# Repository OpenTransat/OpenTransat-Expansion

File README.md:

# OpenTransat-Expansion

The [Navigator](https://github.com/OpenTransat/OpenTransat-Navigator) is mounted on top of Expansion Board that will provide additional functions more specific to the boat. This modular design allows to make quick modifications on the Expansion Board while keeping the more complex Navigation Board unchanged.

## Features

* Watchdog timer that monitors the “heartbeat” of the main CPU. If the Navigator doesn't respond for a minute or it reports any kind of failure, the watchdog will cut power for a few seconds.

* MOSFETs to turn on particular hardware only when needed.

## Boat Hardware Scheme

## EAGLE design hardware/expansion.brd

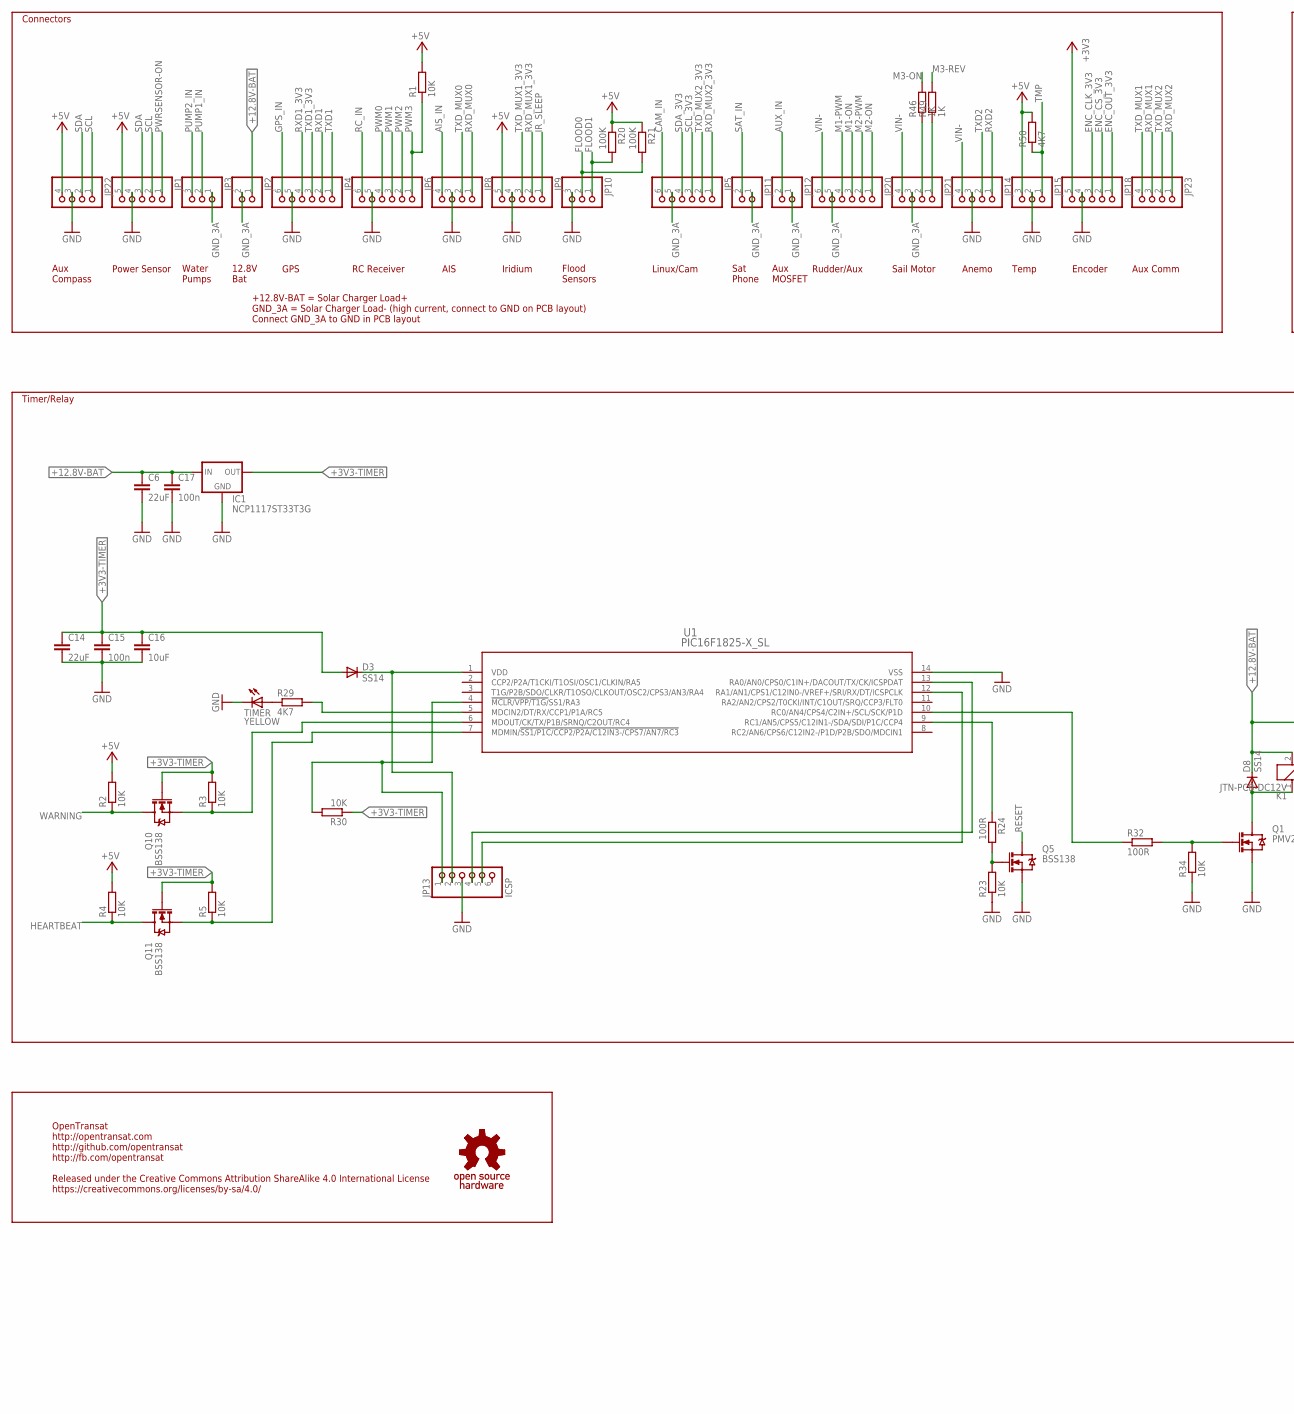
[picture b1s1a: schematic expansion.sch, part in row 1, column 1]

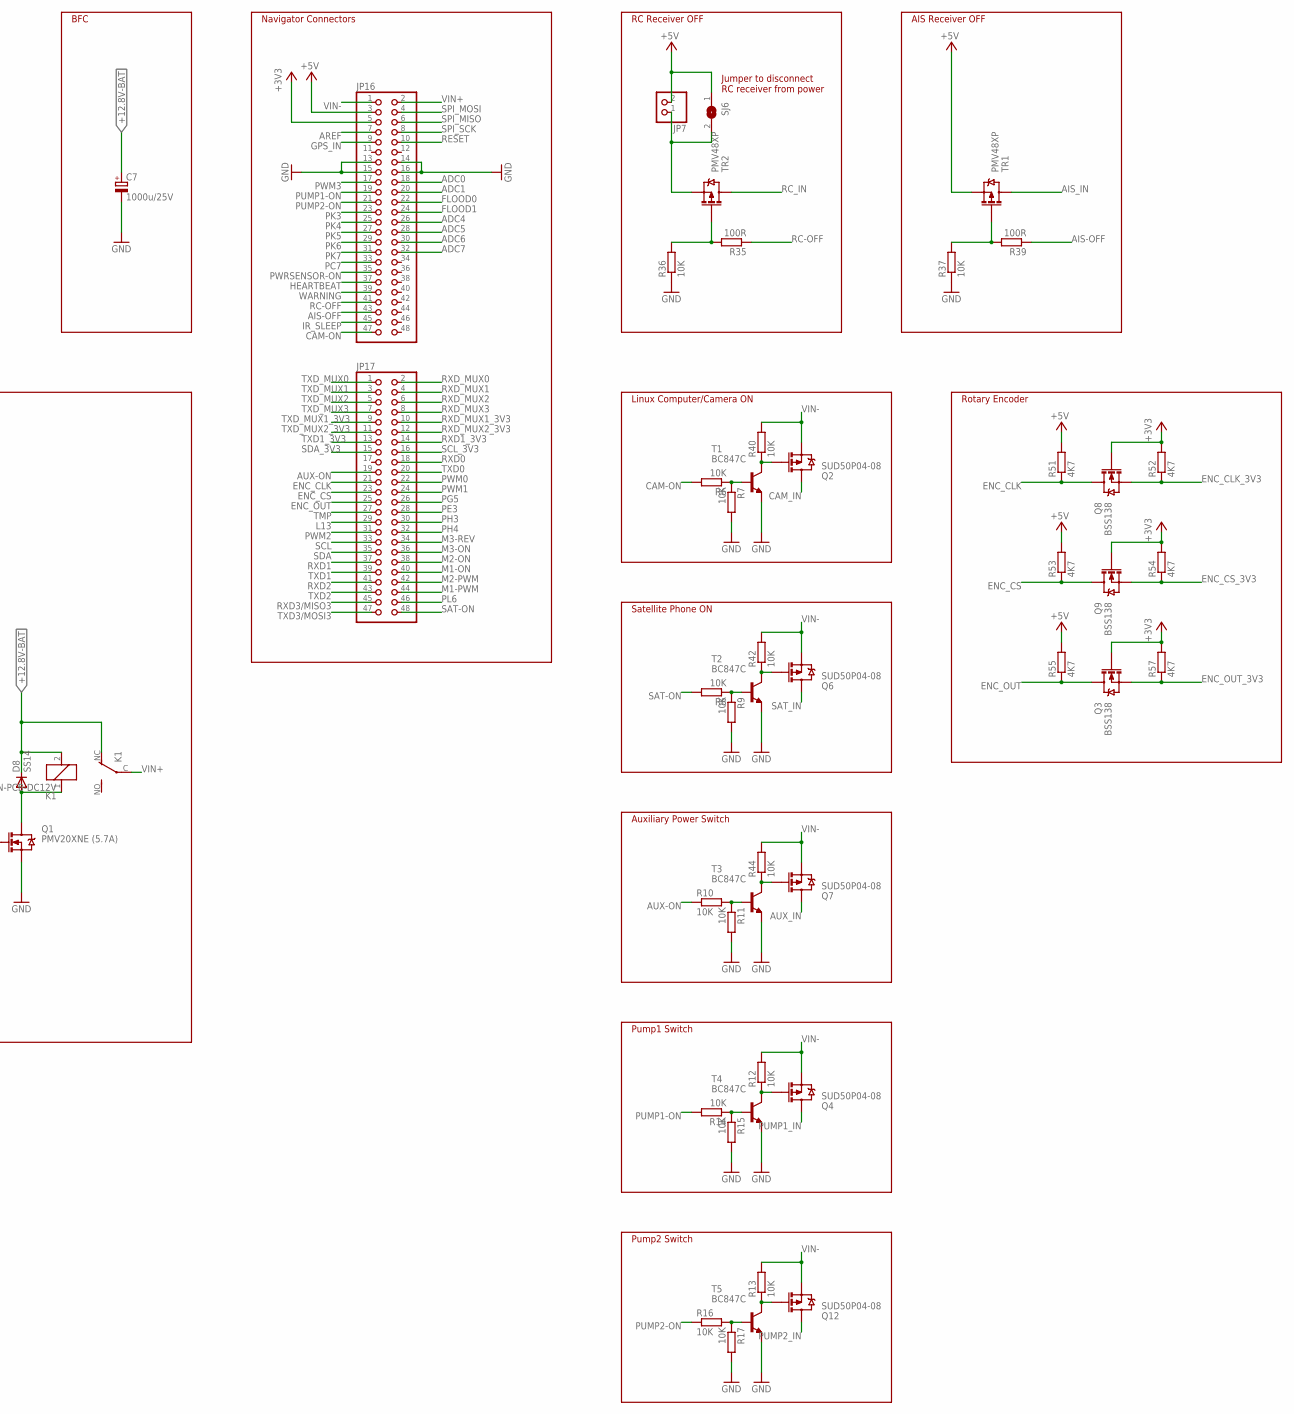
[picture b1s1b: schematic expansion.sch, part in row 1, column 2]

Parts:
C6, C14: 22uF; C1210
C7: 1000u/25V; E5-10,5
C15, C17: 100n; C0603
C16: 10uF; C1206
D3, D8: SS14; DO214AC
IC1: NCP1117ST33T3G; SOT223
JP1, JP9, JP18: PINHD-1X5; 1X05
JP2, JP7, JP11, JP12: PINHD-1X2; 1X02
JP3, JP10, JP15: PINHD-1X3; 1X03
JP4, JP5, JP6, JP20: PINHD-1X6; 1X06
JP8, JP14, JP21, JP22, JP23: PINHD-1X4; 1X04
JP13: ICSP; 1X06
JP16, JP17: PINHD-2X24; 2X24
K1: JTN-PCB-DC12V; JT-PCB
Q1: PMV20XNE (5.7A); SOT23-3
Q2, Q4, Q6, Q7, Q12: SUD50P04-08; D-PAK_TO252AA
Q3, Q5, Q8, Q9, Q10, Q11: BSS138; SOT23-3
R1, R2, R3, R4, R5, R6, R7, R8, R9, R10, R11, R12, R13, R14, R15, R16, R17, R23, R30, R34, R36, R37, R40, R42, R44: 10K; R0603
R20, R21: 100K; R0603
R24, R32, R35, R39: 100R; R0603
R29, R50, R51, R52, R53, R54, R55, R57: 4K7; R0603
R46, R49: 1K; R0603
SJ6: SJ
T1, T2, T3, T4, T5: BC847C; SOT23
TIMER: YELLOW; CHIPLED_0805
TR1, TR2: PMV48XP; SOT23-3
U1: PIC16F1825-X_SL; SOIC14-N_MC
U$2: OSHW; OSHWM

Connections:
+3V3: JP16.5, JP18.5, Q3.1 (G), Q8.1 (G), Q9.1 (G), R52.2, R54.2, R57.2
+3V3-TIMER: C14.1, C15.1, C16.1, D3.A, IC1.2 (OUT), IC1.4 (OUT), Q10.1 (G), Q11.1 (G), R3.2, R5.2, R30.1
+5V: JP1.5, JP7.2, JP9.5, JP15.3, JP16.3, JP22.4, R1.2, R2.2, R4.2, R20.1, R21.1, R50.2, R51.2, R53.2, R55.2, SJ6.1, TR1.2 (S)
+12.8V-BAT: C6.1, C7.+, C17.1, D8.C, IC1.3 (IN), JP2.1, K1.2, K1.NC (O)
ADC0: JP16.18
ADC1: JP16.20
ADC4: JP16.26
ADC5: JP16.28
ADC6: JP16.30
ADC7: JP16.32
AIS-OFF: JP16.43, R39.1
AIS_IN: JP8.4, TR1.3 (D)
AREF: JP16.7
AUX-ON: JP17.19, R10.1
AUX_IN: JP12.2, Q7.2 (D)
CAM-ON: JP16.47, R6.2
CAM_IN: JP5.6, Q2.2 (D)
ENC_CLK: JP17.21, Q8.3 (D), R51.1
ENC_CLK_3V3: JP18.3, Q8.2 (S), R52.1
ENC_CS: JP17.23, Q9.3 (D), R53.1
ENC_CS_3V3: JP18.2, Q9.2 (S), R54.1
ENC_OUT: JP17.25, Q3.3 (D), R55.1
ENC_OUT_3V3: JP18.1, Q3.2 (S), R57.1
FLOOD0: JP10.2, JP16.22, R21.2
FLOOD1: JP10.1, JP16.24, R20.2
GND: C6.2, C7.-, C14.2, C15.2, C16.2, C17.2, IC1.1 (GND), JP1.4, JP4.5, JP6.5, JP8.3, JP9.4, JP10.3, JP13.3, JP14.3, JP15.2, JP16.13, JP16.14, JP16.15, JP16.16, JP18.4, JP22.3, Q1.2 (S), Q5.2 (S), R7.2, R9.2, R11.2, R15.2, R17.2, R23.1, R34.1, R36.1, R37.1, T1.2 (E), T2.2 (E), T3.2 (E), T4.2 (E), T5.2 (E), TIMER.C, U1.14 (VSS)
GND_3A: JP2.2, JP3.1, JP5.5, JP11.1, JP12.1, JP20.5, JP21.3
GPS_IN: JP4.6, JP16.9
HEARTBEAT: JP16.37, Q11.3 (D), R4.1
IR_SLEEP: JP9.1, JP16.45
L13: JP17.29
M1-ON: JP17.40, JP20.3
M1-PWM: JP17.44, JP20.4
M2-ON: JP17.38, JP20.1
M2-PWM: JP17.42, JP20.2
M3-ON: JP17.36, R46.2
M3-REV: JP17.34, R49.2
unnamed: R6.1, R7.1, T1.1 (B)
unnamed: Q10.2 (S), R3.1, U1.6 (MDOUT/CK/TX/P1B/SRNQ/C2OUT/RC4)
unnamed: R8.1, R9.1, T2.1 (B)
unnamed: Q11.2 (S), R5.1, U1.7 (MDMIN/!SS1/P1C/CCP2/P2A/C12IN3-/CPS7/AN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)
unnamed: R10.2, R11.1, T3.1 (B)
unnamed: Q4.1 (G), R12.1, T4.3 (C)
unnamed: Q12.1 (G), R13.1, T5.3 (C)
unnamed: R14.1, R15.1, T4.1 (B)
unnamed: R16.2, R17.1, T5.1 (B)
unnamed: JP21.2, R46.1
unnamed: JP21.1, R49.1
unnamed: JP13.4, U1.13 (RA0/AN0/CPS0/C1IN+/DACOUT/TX/CK/ICSPDAT)
unnamed: Q7.1 (G), R44.1, T3.3 (C)
unnamed: Q6.1 (G), R42.1, T2.3 (C)
unnamed: Q2.1 (G), R40.1, T1.3 (C)
unnamed: JP13.1, R30.2, U1.4 (!MCLR/VPP/T1G/!SS1/RA3)
unnamed: JP13.5, U1.12 (RA1/AN1/CPS1/C12IN0-/VREF+/SRI/RX/DT/IC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)
unnamed: R32.1, U1.10 (RC0/AN4/CPS4/C2IN+/SCL/SCK/P1D)
unnamed: D3.C, JP13.2, U1.1 (VDD)
unnamed: R24.1, U1.9 (RC1/AN5/CPS5/C12IN1-/SDA/SDI/P1C/CCP4)
unnamed: Q5.1 (G), R23.2, R24.2
unnamed: R29.2, U1.5 (MDCIN2/DT/RX/CCP1/P1A/RC5)
unnamed: R29.1, TIMER.A
unnamed: Q1.1 (G), R32.2, R34.2
unnamed: JP7.1, SJ6.2, TR2.2 (S)
unnamed: D8.A, K1.1, Q1.3 (D)
unnamed: R35.2, R36.2, TR2.1 (G)
unnamed: R37.2, R39.2, TR1.1 (G)
PC7: JP16.33
PE3: JP17.28
PG5: JP17.26
PH3: JP17.30
PH4: JP17.32
PK3: JP16.23
PK4: JP16.25
PK5: JP16.27
PK6: JP16.29
PK7: JP16.31
PL6: JP17.46
PUMP1-ON: JP16.19, R14.2
PUMP1_IN: JP3.2, Q4.2 (D)
PUMP2-ON: JP16.21, R16.1
PUMP2_IN: JP3.3, Q12.2 (D)
PWM0: JP6.4, JP17.22
PWM1: JP6.3, JP17.24
PWM2: JP6.2, JP17.31
PWM3: JP6.1, JP16.17, R1.1
PWRSENSOR-ON: JP1.1, JP16.35
RC-OFF: JP16.41, R35.1
RC_IN: JP6.6, TR2.3 (D)
RESET: JP16.10, Q5.3 (D)
RXD0: JP17.18
RXD1: JP4.2, JP17.37
RXD1_3V3: JP4.4, JP17.14
RXD2: JP14.1, JP17.41
RXD3/MISO3: JP17.45
RXD_MUX0: JP8.1, JP17.2
RXD_MUX1: JP17.4, JP23.3
RXD_MUX1_3V3: JP9.2, JP17.10
RXD_MUX2: JP17.6, JP23.1
RXD_MUX2_3V3: JP5.1, JP17.12
RXD_MUX3: JP17.8
SAT-ON: JP17.48, R8.2
SAT_IN: JP11.2, Q6.2 (D)
SCL: JP1.2, JP17.33, JP22.1
SCL_3V3: JP5.3, JP17.16
SDA: JP1.3, JP17.35, JP22.2
SDA_3V3: JP5.4, JP17.15
SPI_MISO: JP16.6
SPI_MOSI: JP16.4
SPI_SCK: JP16.8
TMP: JP15.1, JP17.27, R50.1
TXD0: JP17.20
TXD1: JP4.1, JP17.39
TXD1_3V3: JP4.3, JP17.13
TXD2: JP14.2, JP17.43
TXD3/MOSI3: JP17.47
TXD_MUX0: JP8.2, JP17.1
TXD_MUX1: JP17.3, JP23.4
TXD_MUX1_3V3: JP9.3, JP17.9
TXD_MUX2: JP17.5, JP23.2
TXD_MUX2_3V3: JP5.2, JP17.11
TXD_MUX3: JP17.7
VIN+: JP16.2, K1.C
VIN-: JP14.4, JP16.1, JP20.6, JP21.4, Q2.3 (S), Q4.3 (S), Q6.3 (S), Q7.3 (S), Q12.3 (S), R12.2, R13.2, R40.2, R42.2, R44.2
WARNING: JP16.39, Q10.3 (D), R2.1

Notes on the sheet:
Navigator Connectors
Connectors
Timer/Relay
RC Receiver OFF
AIS Receiver OFF
Linux Computer/Camera ON
Satellite Phone ON
Auxiliary Power Switch
Rotary Encoder
12.8V Bat
GPS
RC Receiver
AIS
Iridium
Flood Sensors
Linux/Cam
Sat Phone
Aux MOSFET
Rudder/Aux
Sail Motor
Anemo
Temp
Encoder
Aux Comm
+12.8V-BAT = Solar Charger Load+ GND_3A = Solar Charger Load- (high current, connect to GND on PCB layout) Connect GND_3A to GND in PCB layout
Water Pumps
BFC
OpenTransat http://opentransat.com http://github.com/opentransat http://fb.com/opentransat Released under the Creative Commons Attribution ShareAlike 4.0 International License https://creativecommons.org/licenses/by-sa/4.0/
Jumper to disconnect RC receiver from power
Pump1 Switch
Pump2 Switch
Aux Compass
Power Sensor

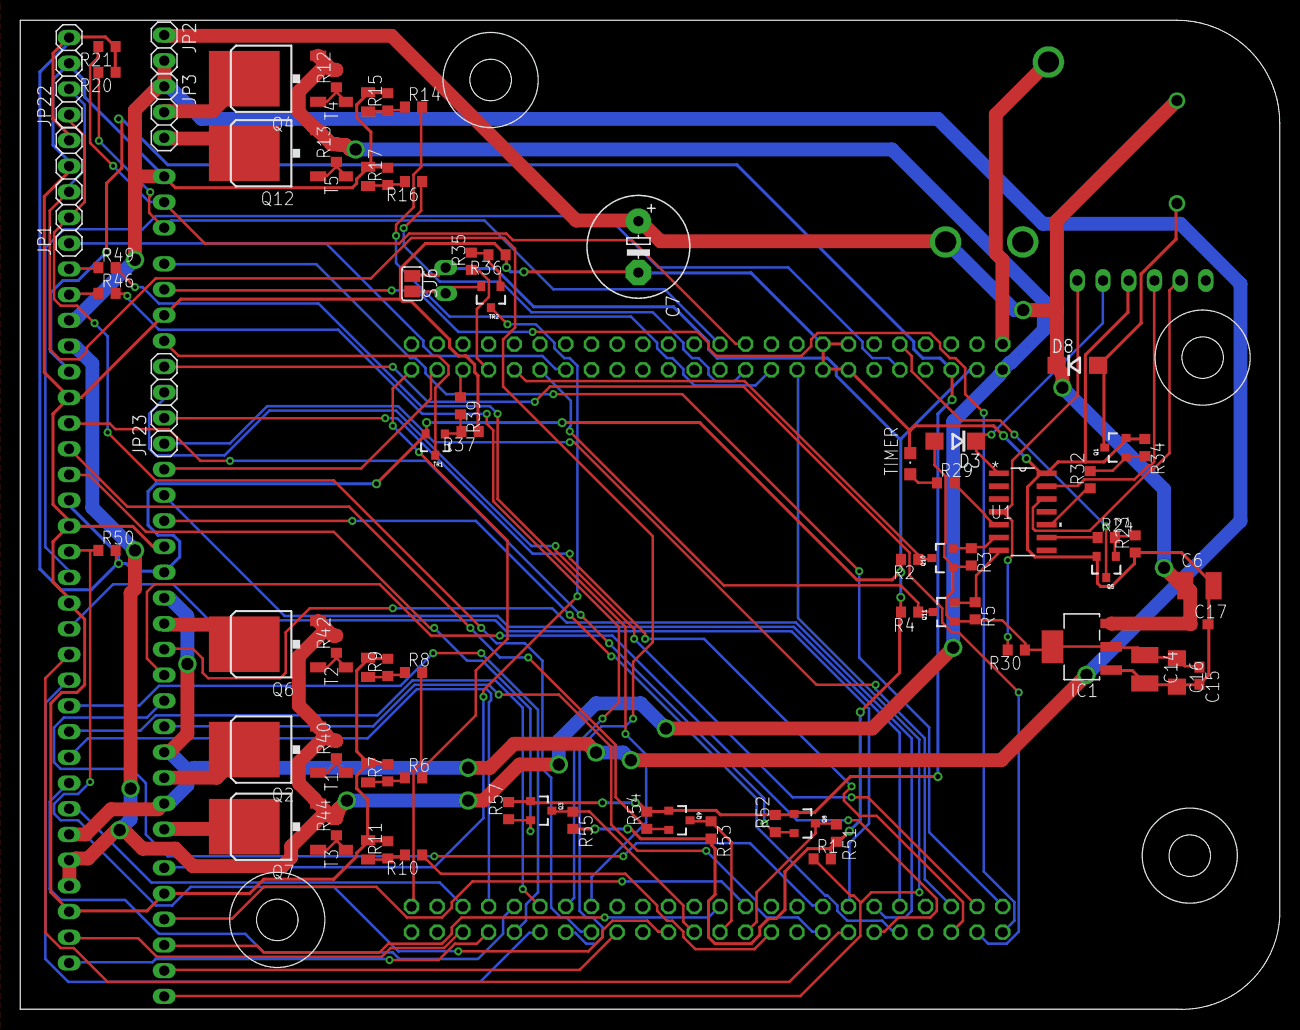
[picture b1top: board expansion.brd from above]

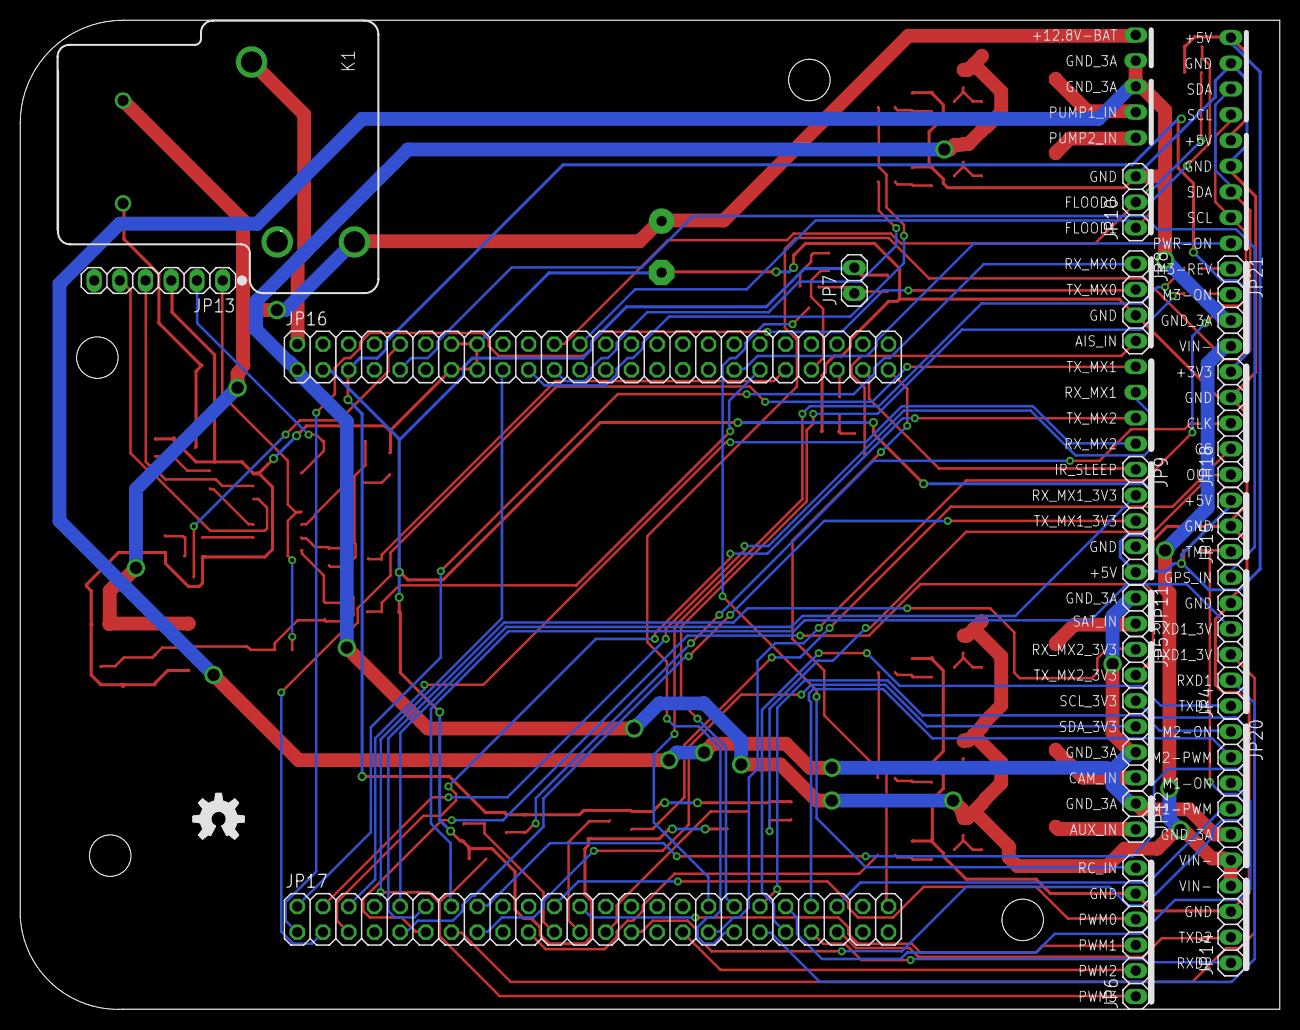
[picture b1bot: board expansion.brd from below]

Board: 2 copper layers, 124.5 x 97.7 mm, 96 parts (18 on the bottom side), 95 nets.

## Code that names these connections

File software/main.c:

/*
Hardware watchdog timer based on PIC16F1825

OpenTransat
http://opentransat.com
http://github.com/opentransat
http://fb.com/opentransat

Released under the Creative Commons Attribution ShareAlike 4.0 International License
https://creativecommons.org/licenses/by-sa/4.0/
*/

#define _XTAL_FREQ 31000UL
#include "config.h"
#include <xc.h>

#define RELAY PORTCbits.RC0
#define NAVRESET PORTCbits.RC1
#define HEARTBEAT PORTCbits.RC3
#define WARNING PORTCbits.RC4
#define LED PORTCbits.RC5

#define TMR1INIT (65535 - 31000) //timer1 increments +31000 per second

#define RESET_AFTER_SEC 60 //reset after no heartbeat
//#define RESET_AFTER_SEC 15 //TESTING reset after no heartbeat

#define RELAY_AFTER_SEC 24UL*3600UL //periodically turn off the whole boat
//#define RELAY_AFTER_SEC 60 //TESTING periodically turn off the whole boat

#define WARNING_SEC 30 //WARNING pin LOW a number of seconds before relay shutdown

#define RESET_US 200

#define RELAY_SEC 15 //turn off time, discharge all capacitors
//#define RELAY_SEC 10 //TESTING turn off time, discharge all capacitors

volatile unsigned long sectimer1, sectimer2; //incrementing each second in timer1 interrupt

void init_io() {
    OSCCONbits.IRCF = 0b0000; //31kHz oscillator
    TRISA = 0;
    PORTA = 0;
    TRISC = 0b00001000; //RC0 = RELAY (active high), RC1 = NAVRESET (active high), RC3 = HARTBEAT (input), RC4 = WARNING (active low), RC5 = LED (active high)
    PORTC = 0b00010000;
    
    //timer1 for detecting heartbeat
    T1CONbits.TMR1CS = 0b01; //increment on Fosc
    T1CONbits.T1CKPS = 0b00; //prescaler 1:1
    T1CONbits.TMR1ON = 1;
    
    //enable interrupts for timer1
    PIR1bits.TMR1IF = 0; //interrupt flag should be cleared before enabling interrupts (page 195 http://ww1.microchip.com/downloads/en/DeviceDoc/41440A.pdf)
    PIE1bits.TMR1IE = 1;
    INTCONbits.PEIE = 1;
    INTCONbits.GIE = 1;

    //disable all analog ports
    ANSELA = 0;
    ANSELC = 0;

    //disable some peripherals
    CM1CON0bits.C1ON = 0;
    CM2CON0bits.C2ON = 0;
    RCSTAbits.SPEN = 0;    
}

void delay_sec(unsigned int n) {
    while (n--) {
        CLRWDT();
        LED = LED?0:1;
        __delay_ms(1000);
    }
}

void navreset() {
    NAVRESET = 1;
    __delay_us(RESET_US);    
    NAVRESET = 0;
}

void relay_reset(unsigned int sec) {
    RELAY = 1;
    delay_sec(sec);
    RELAY = 0;
}

void interrupt timer1_interrupt(void) {
    if(PIR1bits.TMR1IF && PIE1bits.TMR1IE) {
        sectimer1++;
        sectimer2++;
        TMR1 = TMR1INIT;
        PIR1bits.TMR1IF = 0;
    }
}

void main(void) {

    init_io();

    char hb, hb_prev;
    sectimer1 = 0;
    sectimer2 = 0;
    TMR1 = TMR1INIT;
    
    while(1) {
        CLRWDT();
        
        hb = HEARTBEAT;

        if (hb != hb_prev) { //heartbeat detected: reset sectimer1
            sectimer1 = 0;
            LED = 1;
            __delay_ms(10);
            LED = 0;
        }
        
        if (sectimer1 > RESET_AFTER_SEC) { //no heartbeat: reset master CPU (no warning)
            navreset();
            sectimer1 = 0;
            LED = 1;
            __delay_ms(10);
            LED = 0;
        }
        
        if (sectimer2 > RELAY_AFTER_SEC) { //relay shutdown every RELAY_AFTER_SEC seconds
            WARNING = 0;
            delay_sec(WARNING_SEC);
            relay_reset(RELAY_SEC);
            WARNING = 1;
            __delay_ms(100);
            navreset();
            sectimer1 = 0;
            sectimer2 = 0;
            LED = 1;
            __delay_ms(10);
            LED = 0;
        }
        
        hb_prev = hb;

    }
    return;
}
